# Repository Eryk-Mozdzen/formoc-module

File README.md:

# Field Oriented Motor Controller | FORMOC module
BLDC motor controller using FOC algorithm by Wojciech Bohdan and Eryk Możdżeń.

## Project overview
The goal is to create an opportunity for easy implementation of BLDC motors to small autonomous robots like linefollower or minisumo.

Right now project is in mid development stage.

## Interface

```c
struct {
  uint8_t fdc : 5;  // field code
  uint8_t tg  : 1;  // toggle
  uint8_t rw  : 1;  // read/write operation
  uint8_t mot : 1;  // left/right motor
} msg_header_tx;

struct {
  uint8_t fdc : 5;  // field code
  uint8_t tg  : 1;  // toggle
  uint8_t un  : 1;  // unused
  uint8_t mot : 1;  // left/right motor
} msg_header_rx;

struct {
  uint8_t sta : 7;  // status field
  uint8_t tg  : 1;  // toggle
} msg_hearbeat;
```

| Field                 | Code  | R/W    | Type          | Unit      | Details |
| -----                 | ----  | ---    | ----          | ----      | ------- |
| status                | 0x00  | r/w    | `uint8_t`     |           | bit 0 - MCP8024 error flag <br>bit 1 - read/write access error flag <br> bit 2 - read/write wrong toggle flag <br>  bit 3 - write timeout flag <br> bit 4 - write wrong param flag <br> bit 5-6 (unused) <br> bit 7 (reserved)        |
| control (toggle free)               | 0x01  | w    | `uint8_t`     |           | bit 0 - reset <br> bit 1-7 (unused)         |
|||||||
| hardware config          | 0x0A  | r/w    | `uint8_t` <br> `uint16_t` <br> `uint16_t` | <br> count <br> count         | motor pole pairs <br> encoder CPR <br> encoder offset  |
| Id controller config          | 0x0B  | r/w    | `float32_t` <br> `float32_t` <br> `float32_t` ||  Kp <br> Ki <br> Kd |
| Iq controller config          | 0x0C  | r/w    | `float32_t` <br> `float32_t` <br> `float32_t` ||  Kp <br> Ki <br> Kd |
| velocity controller config          | 0x0D  | r/w    | `float32_t` <br> `float32_t` <br> `float32_t` ||  Kp <br> Ki <br> Kd |
|||||||
| velocity setpoint     | 0x11 | w      | `float32_t`   | rps       |           |
|||||||
| rotor position        | 0x20 | r      | `int32_t`     | count     |
| rotor velocity        | 0x21 | r      | `float32_t`   | rps       |           |
| power supply voltage  | 0x23 | r      | `uint16_t`    | mV        |           |
|||||||
| torque limit          | 0x30 | w      | `float32_t`   | Nm        |           |
| velocity limit        | 0x31 | w      | `float32_t`   | rps       |           |

# TODO
- check voltages
- solder cables
- one-way, reliable communication
- GET RID OF OVERCURRENT "PROTECTION"
- improve PID tunning
- find torque measurement method
- improve code organization
- add interface

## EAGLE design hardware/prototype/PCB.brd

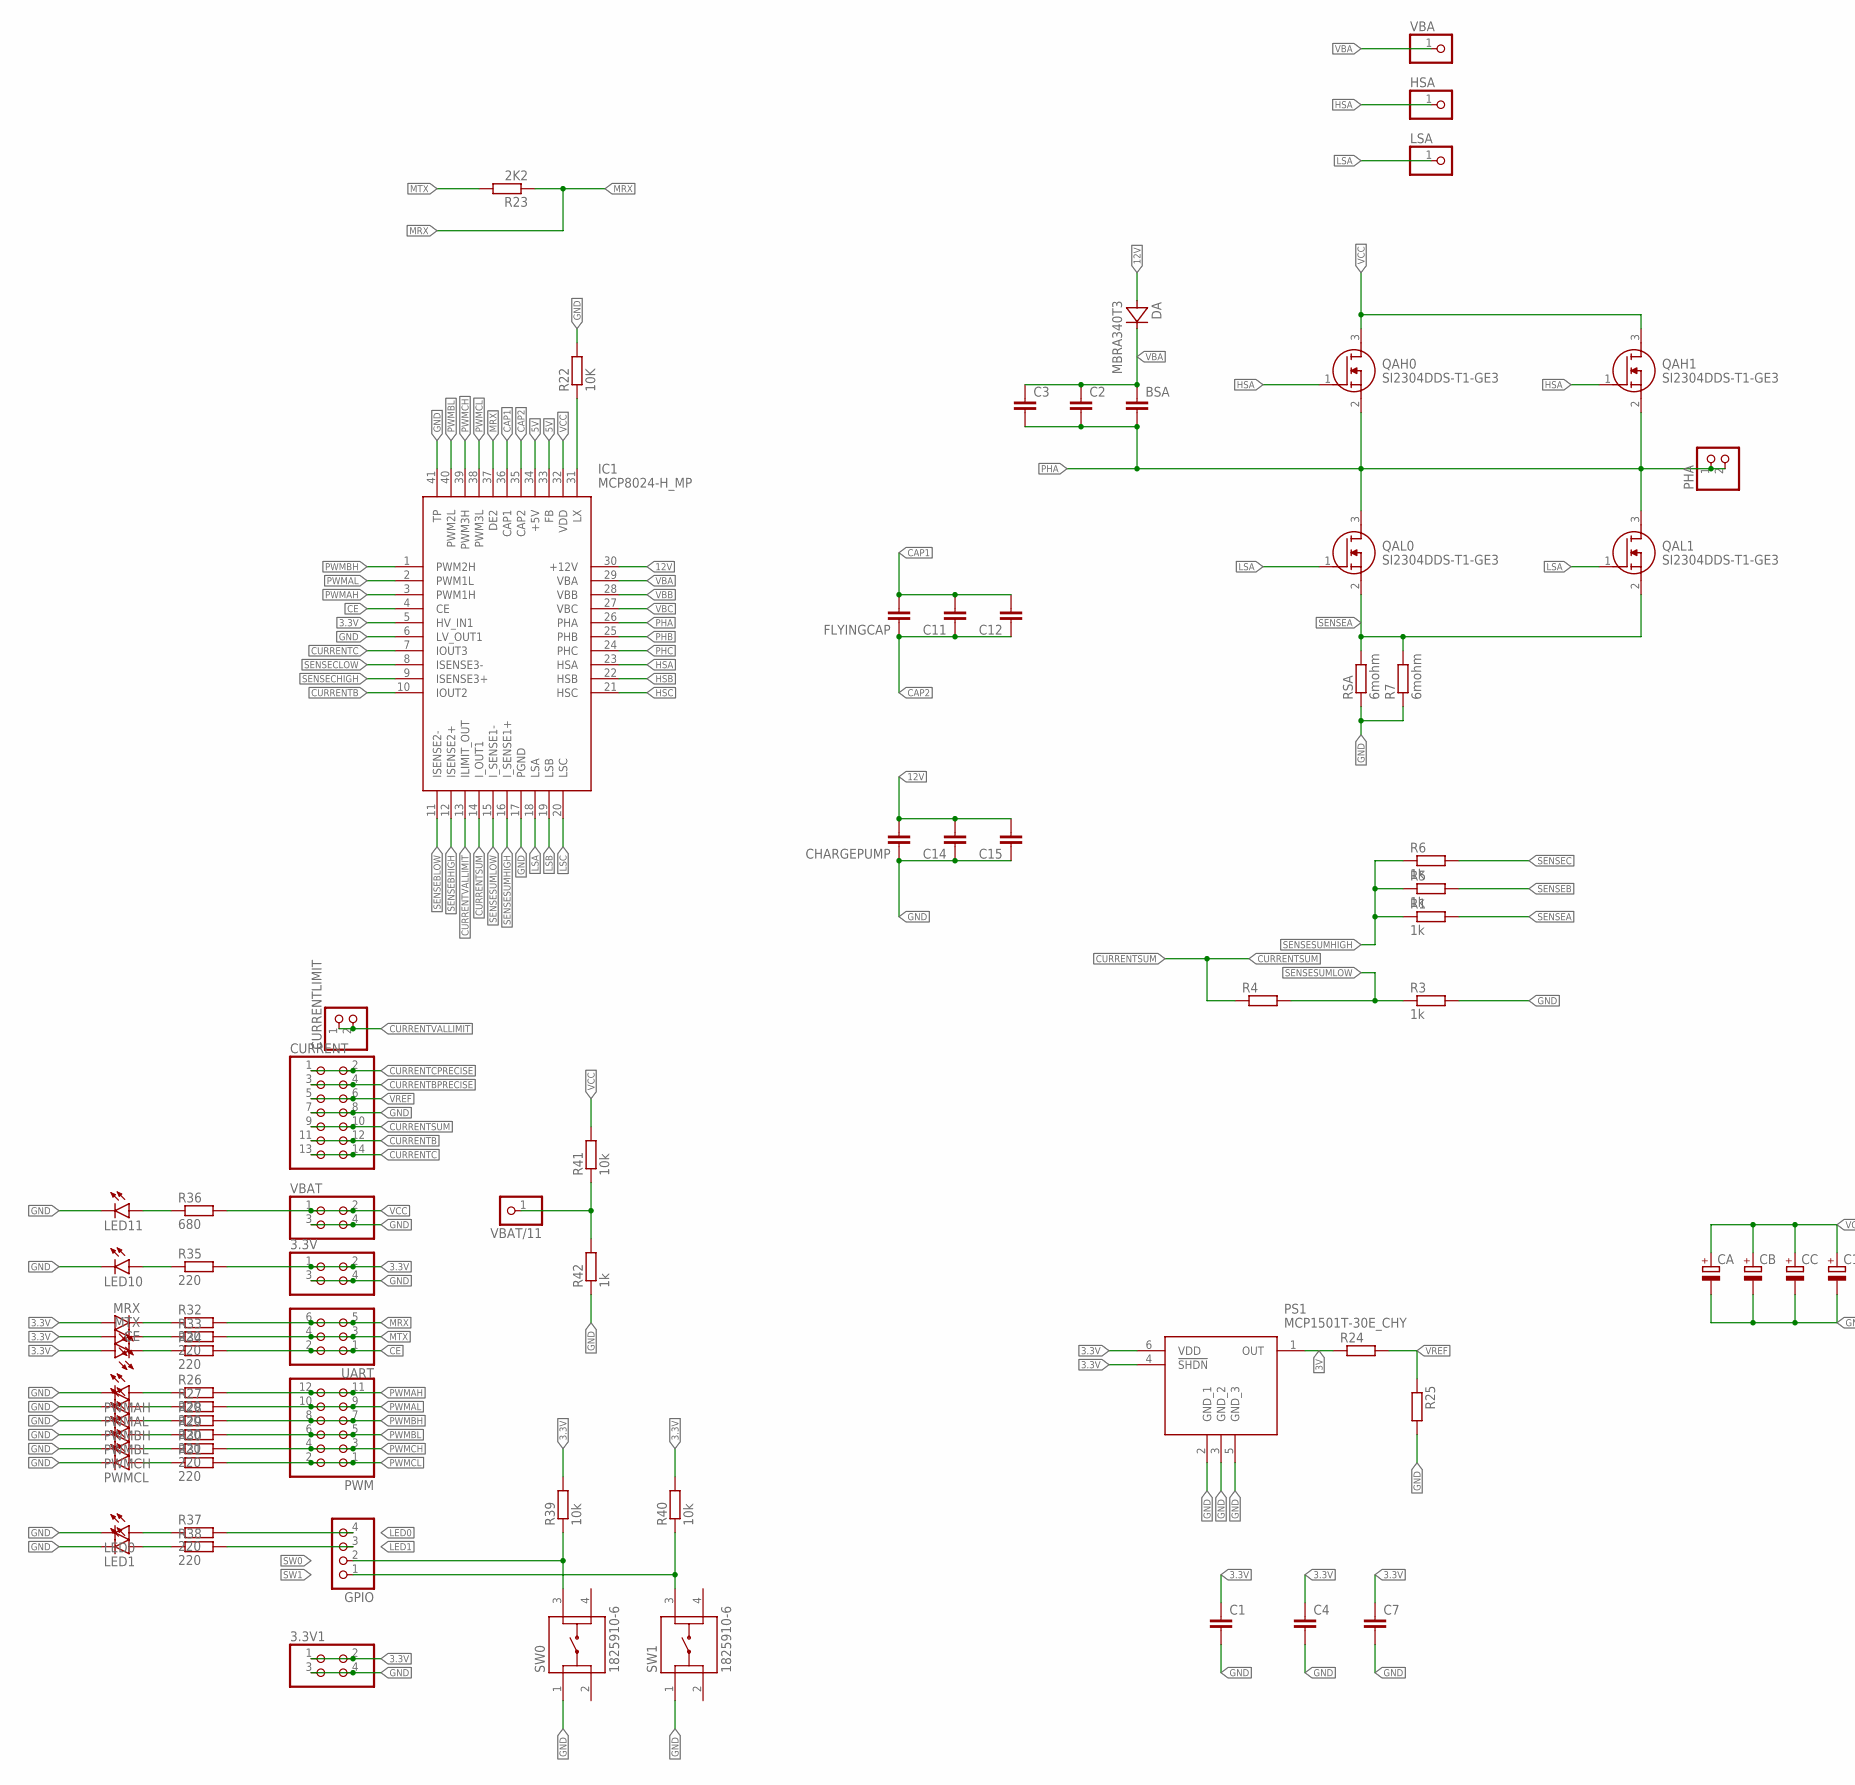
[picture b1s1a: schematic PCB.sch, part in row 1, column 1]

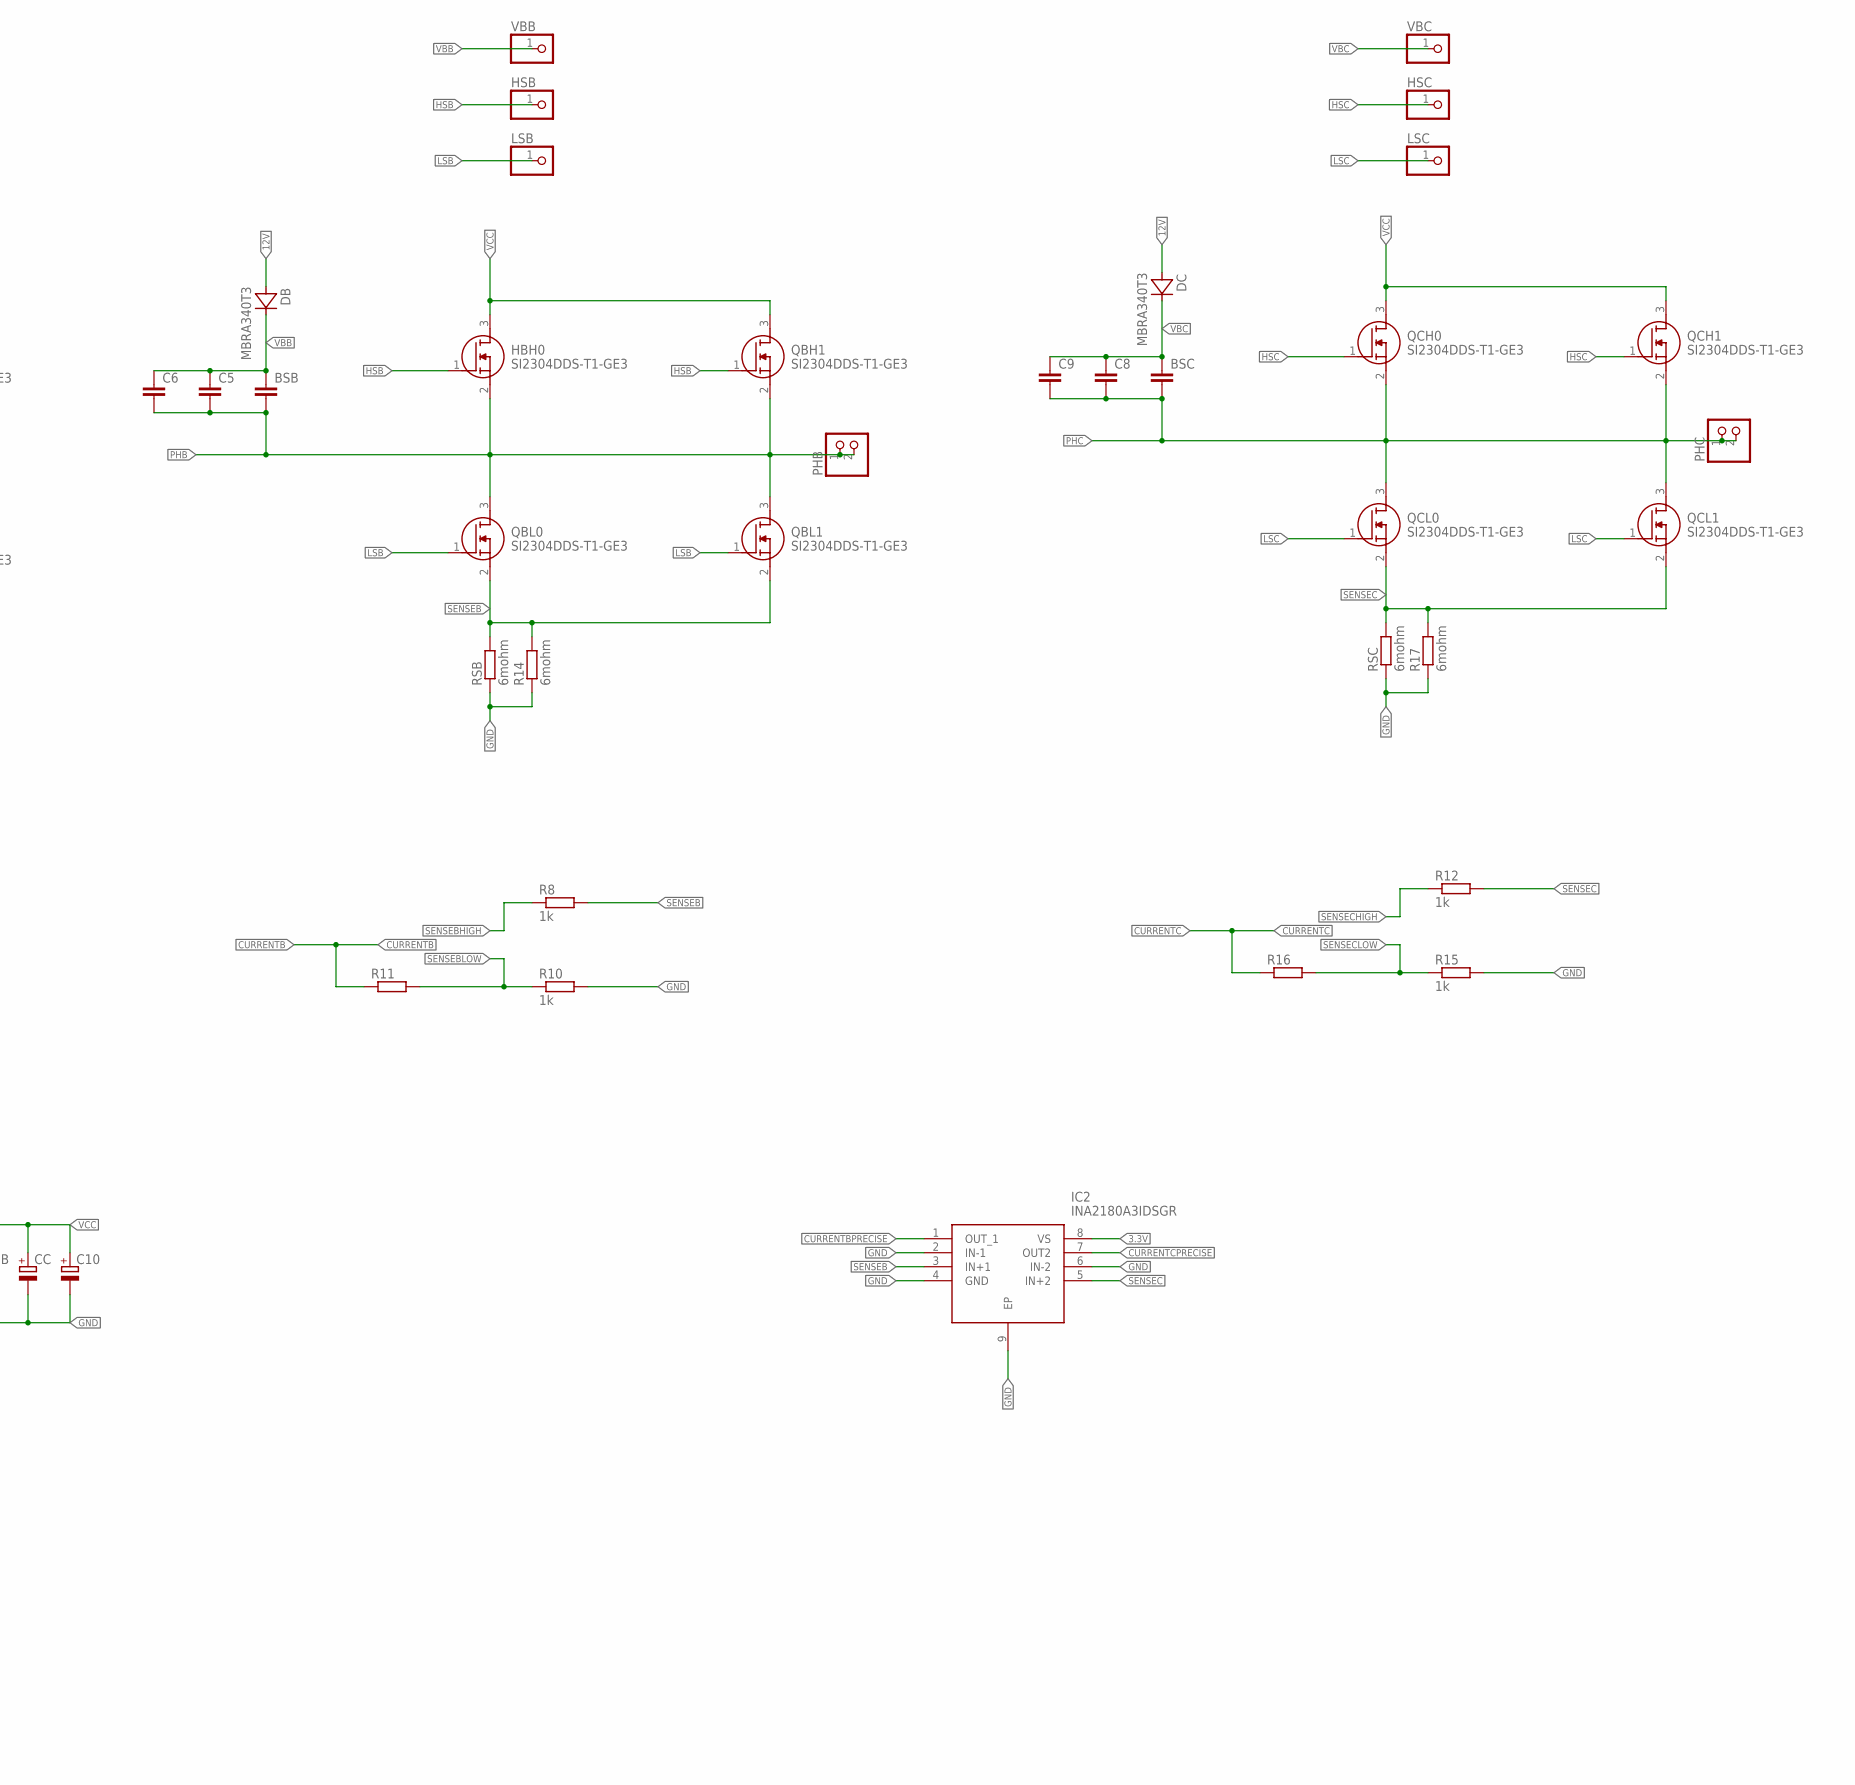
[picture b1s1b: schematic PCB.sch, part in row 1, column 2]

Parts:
3.3V, 3.3V1: PINHD-2X2; 2X02
BSA: C-EUC0603; C0603
BSB: C-EUC0603; C0603
BSC: C-EUC0603; C0603
C1, C2, C3, C4, C5, C6, C7, C8, C9, C11, C12, C14, C15: C-EUC0603; C0603
C10: CPOL-EUE3.5-8; E3,5-8
CA: CPOL-EUE3.5-8; E3,5-8
CB: CPOL-EUE3.5-8; E3,5-8
CC: CPOL-EUE3.5-8; E3,5-8
CE: LEDCHIPLED_0805; CHIPLED_0805
CHARGEPUMP: C-EUC0603; C0603
CURRENT: PINHD-2X7; 2X07
CURRENTLIMIT: PINHD-1X2; 1X02
DA: MBRA340T3; SMA
DB: MBRA340T3; SMA
DC: MBRA340T3; SMA
FLYINGCAP: C-EUC0603; C0603
GPIO: PINHD-1X4; 1X04
HBH0: SI2304DDS-T1-GE3; SOT95P237X112-3N
HSA: PINHD-1X1; 1X01
HSB: PINHD-1X1; 1X01
HSC: PINHD-1X1; 1X01
IC1: MCP8024-H_MP; QFN40P500X500X90-41N
IC2: INA2180A3IDSGR; SON50P200X200X80-9N
LED0, LED1, LED10, LED11: LEDCHIPLED_0805; CHIPLED_0805
LSA: PINHD-1X1; 1X01
LSB: PINHD-1X1; 1X01
LSC: PINHD-1X1; 1X01
MRX: LEDCHIPLED_0805; CHIPLED_0805
MTX: LEDCHIPLED_0805; CHIPLED_0805
PHA: PINHD-1X2; 1X02
PHB: PINHD-1X2; 1X02
PHC: PINHD-1X2; 1X02
PS1: MCP1501T-30E_CHY; SOT95P270X145-6N
PWM: PINHD-2X6; 2X06
PWMAH: LEDCHIPLED_0805; CHIPLED_0805
PWMAL: LEDCHIPLED_0805; CHIPLED_0805
PWMBH: LEDCHIPLED_0805; CHIPLED_0805
PWMBL: LEDCHIPLED_0805; CHIPLED_0805
PWMCH: LEDCHIPLED_0805; CHIPLED_0805
PWMCL: LEDCHIPLED_0805; CHIPLED_0805
QAH0, QAH1: SI2304DDS-T1-GE3; SOT95P237X112-3N
QAL0, QAL1: SI2304DDS-T1-GE3; SOT95P237X112-3N
QBH1: SI2304DDS-T1-GE3; SOT95P237X112-3N
QBL0, QBL1: SI2304DDS-T1-GE3; SOT95P237X112-3N
QCH0, QCH1: SI2304DDS-T1-GE3; SOT95P237X112-3N
QCL0, QCL1: SI2304DDS-T1-GE3; SOT95P237X112-3N
R1, R3, R5, R6, R8, R10, R12, R15, R42: 1k; R0805
R4, R11, R16, R24, R25: R-EU_R0805; R0805
R7, R14, R17: 6mohm; R1206
R22: 10K; R0805
R23: 2K2; R0805
R26, R27, R28, R29, R30, R31, R32, R33, R34, R35, R37, R38: 220; R0805
R36: 680; R0805
R39, R40, R41: 10k; R0805
RSA: 6mohm; R1206
RSB: 6mohm; R1206
RSC: 6mohm; R1206
SW0, SW1: 1825910-6
UART: PINHD-2X3; 2X03
VBA: PINHD-1X1; 1X01
VBAT: PINHD-2X2; 2X02
VBAT/11: PINHD-1X1; 1X01
VBB: PINHD-1X1; 1X01
VBC: PINHD-1X1; 1X01

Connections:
3.3V: 3.3V.1, 3.3V.2, 3.3V1.1, 3.3V1.2, C1.1, C4.1, C7.1, CE.A, IC1.5 (HV_IN1), IC2.8 (VS), MRX.A, MTX.A, PS1.4 (!SHDN), PS1.6 (VDD), R35.2, R39.2, R40.2
3V: PS1.1 (OUT), R24.1
5V: IC1.33 (FB), IC1.34 (+5V)
12V: C14.2, C15.2, CHARGEPUMP.2, DA.A, DB.A, DC.A, IC1.30 (+12V)
CAP1: C11.2, C12.2, FLYINGCAP.2, IC1.36 (CAP1)
CAP2: C11.1, C12.1, FLYINGCAP.1, IC1.35 (CAP2)
CE: IC1.4 (CE), R34.2, UART.1, UART.2
CURRENTB: CURRENT.11, CURRENT.12, IC1.10 (IOUT2), R11.1
CURRENTBPRECISE: CURRENT.3, CURRENT.4, IC2.1 (OUT_1)
CURRENTC: CURRENT.13, CURRENT.14, IC1.7 (IOUT3), R16.1
CURRENTCPRECISE: CURRENT.1, CURRENT.2, IC2.7 (OUT2)
CURRENTSUM: CURRENT.9, CURRENT.10, IC1.14 (I_OUT1), R4.1
CURRENTVALLIMIT: CURRENTLIMIT.1, CURRENTLIMIT.2, IC1.13 (ILIMIT_OUT)
GND: 3.3V.3, 3.3V.4, 3.3V1.3, 3.3V1.4, C1.2, C4.2, C7.2, C10.-, C14.1, C15.1, CA.-, CB.-, CC.-, CHARGEPUMP.1, CURRENT.7, CURRENT.8, IC1.6 (LV_OUT1), IC1.17 (PGND), IC1.41 (TP), IC2.2 (IN-1), IC2.4 (GND), IC2.6 (IN-2), IC2.9 (EP), LED0.C, LED1.C, LED10.C, LED11.C, PS1.2 (GND_1), PS1.3 (GND_2), PS1.5 (GND_3), PWMAH.C, PWMAL.C, PWMBH.C, PWMBL.C, PWMCH.C, PWMCL.C, R3.2, R7.1, R10.2, R14.1, R15.2, R17.1, R22.2, R25.2, R42.1, RSA.1, RSB.1, RSC.1, SW0.1, SW1.1, VBAT.3, VBAT.4
HSA: HSA.1, IC1.23 (HSA), QAH0.1 (G), QAH1.1 (G)
HSB: HBH0.1 (G), HSB.1, IC1.22 (HSB), QBH1.1 (G)
HSC: HSC.1, IC1.21 (HSC), QCH0.1 (G), QCH1.1 (G)
LED0: GPIO.4, R37.2
LED1: GPIO.3, R38.2
LSA: IC1.18 (LSA), LSA.1, QAL0.1 (G), QAL1.1 (G)
LSB: IC1.19 (LSB), LSB.1, QBL0.1 (G), QBL1.1 (G)
LSC: IC1.20 (LSC), LSC.1, QCL0.1 (G), QCL1.1 (G)
MRX: IC1.37 (DE2), R23.1, R32.2, UART.5, UART.6
MTX: R23.2, R33.2, UART.3, UART.4
unnamed: IC1.31 (LX), R22.1
unnamed: PWMAH.A, R26.1
unnamed: PWMAL.A, R27.1
unnamed: PWMBH.A, R28.1
unnamed: PWMBL.A, R29.1
unnamed: PWMCH.A, R30.1
unnamed: PWMCL.A, R31.1
unnamed: MRX.C, R32.1
unnamed: MTX.C, R33.1
unnamed: CE.C, R34.1
unnamed: LED10.A, R35.1
unnamed: LED11.A, R36.1
unnamed: LED0.A, R37.1
unnamed: LED1.A, R38.1
unnamed: R41.1, R42.2, VBAT/11.1
PHA: BSA.2, C2.2, C3.2, IC1.26 (PHA), PHA.1, PHA.2, QAH0.2 (S), QAH1.2 (S), QAL0.3 (D), QAL1.3 (D)
PHB: BSB.2, C5.2, C6.2, HBH0.2 (S), IC1.25 (PHB), PHB.1, PHB.2, QBH1.2 (S), QBL0.3 (D), QBL1.3 (D)
PHC: BSC.2, C8.2, C9.2, IC1.24 (PHC), PHC.1, PHC.2, QCH0.2 (S), QCH1.2 (S), QCL0.3 (D), QCL1.3 (D)
PWMAH: IC1.3 (PWM1H), PWM.11, PWM.12, R26.2
PWMAL: IC1.2 (PWM1L), PWM.9, PWM.10, R27.2
PWMBH: IC1.1 (PWM2H), PWM.7, PWM.8, R28.2
PWMBL: IC1.40 (PWM2L), PWM.5, PWM.6, R29.2
PWMCH: IC1.39 (PWM3H), PWM.3, PWM.4, R30.2
PWMCL: IC1.38 (PWM3L), PWM.1, PWM.2, R31.2
SENSEA: QAL0.2 (S), QAL1.2 (S), R1.2, R7.2, RSA.2
SENSEB: IC2.3 (IN+1), QBL0.2 (S), QBL1.2 (S), R5.2, R8.2, R14.2, RSB.2
SENSEBHIGH: IC1.12 (ISENSE2+), R8.1
SENSEBLOW: IC1.11 (ISENSE2-), R10.1, R11.2
SENSEC: IC2.5 (IN+2), QCL0.2 (S), QCL1.2 (S), R6.2, R12.2, R17.2, RSC.2
SENSECHIGH: IC1.9 (ISENSE3+), R12.1
SENSECLOW: IC1.8 (ISENSE3-), R15.1, R16.2
SENSESUMHIGH: IC1.16 (I_SENSE1+), R1.1, R5.1, R6.1
SENSESUMLOW: IC1.15 (I_SENSE1-), R3.1, R4.2
SW0: GPIO.2, R39.1, SW0.3
SW1: GPIO.1, R40.1, SW1.3
VBA: BSA.1, C2.1, C3.1, DA.C, IC1.29 (VBA), VBA.1
VBB: BSB.1, C5.1, C6.1, DB.C, IC1.28 (VBB), VBB.1
VBC: BSC.1, C8.1, C9.1, DC.C, IC1.27 (VBC), VBC.1
VCC: C10.+, CA.+, CB.+, CC.+, HBH0.3 (D), IC1.32 (VDD), QAH0.3 (D), QAH1.3 (D), QBH1.3 (D), QCH0.3 (D), QCH1.3 (D), R36.2, R41.2, VBAT.1, VBAT.2
VREF: CURRENT.5, CURRENT.6, R24.2, R25.1

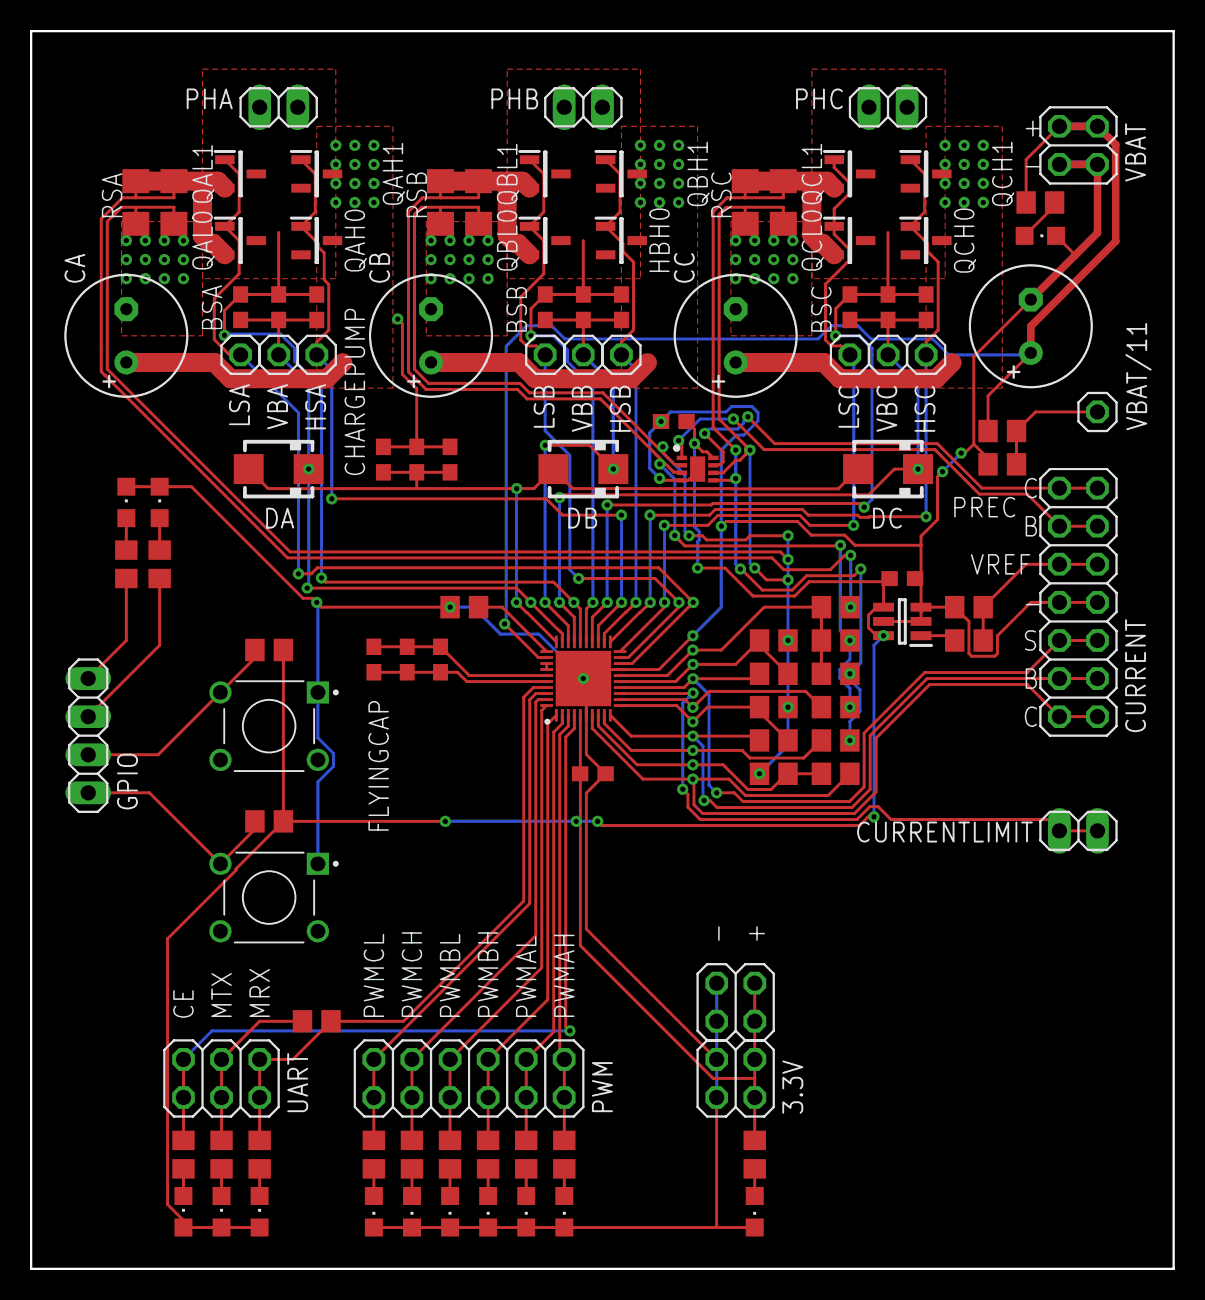
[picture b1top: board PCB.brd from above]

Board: 2 copper layers, 76.2 x 82.5 mm, 114 parts (0 on the bottom side), 64 nets.

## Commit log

2022-01-28 Add prototype hardware
2022-01-29 Add caps.txt in prototype
2022-01-29 Add amplifiers calculations
2022-01-29 Add linefollower motors calculations
2022-02-03 communication on progress
2022-02-04 first spinning
2022-02-04 close loop comutation table
2022-02-08 communication in progres
2022-02-08 communication works
2022-02-08 tools for register data
2022-02-08 cleaning and register union
2022-02-08 phase current sense
2022-02-08 rotor position utilities
2022-02-08 add source files from previous attempts
2022-02-08 time base update
2022-02-11 communication through DMA
2022-02-11 cleaning
2022-02-11 periodic callbacks
2022-03-05 current sensing tests
2022-03-05 simple FOC works!
2022-03-05 fully working simple FOC
2022-03-05 correct interrupt for current sense
2022-03-05 current sensing preparation
2022-03-11 DMA ADC conversion in right moment
2022-03-11 testing
2022-03-11 begin of real FOC
2022-03-11 PIDs constants and encoder offset
2022-03-11 PID tunning
2022-03-12 add photos and TODO list
2022-03-12 add table of field codes
2022-03-12 update field table
2022-03-13 calculations optimalization
2022-03-13 add CMSIS DSP lib
2022-04-22 add bare-metal setup
2022-04-22 uC datasheet and clock needs fix
2022-04-22 nie działa
2022-04-22 phase current work
2022-07-09 Add photos and videos
